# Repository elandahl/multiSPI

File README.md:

# multiSPI
Multiple SPI Devices on a Raspberry Pi

## Description:

Circuit diagram and software to use multiple (> 2) SPI devices on a Raspberry Pi.  This approach uses a shift register to address a demultiplexer which in turn routes up to eight chip selects.  All devices share the same MISO, MOSI, and SCLK.  The Raspberry Pi chip select CE0 is used for SPI communication to the selected device, whereas chip select CE1 is used for latching the shift register.  The particular SPI devices used in this design for demonstration purposes are four 10 bit, 4 differential channel MCP3008 Analog-to-Digital Converters.  Differential voltage measurement is implemented, although the 4 differential measurements could be replaced with eight single inputs.  Another four SPI devices could be added, and this could be further extended with a second demultiplexer to 16 devices.  An additional shft register could be added after the first for essentially unlimited extension to arbitrary numbers of SPI devices.  This same approach could be extended to other platforms such as a microcontroller.

## Author:

Eric Landahl, elandahl@gmail.com

## Acknowledgements:

Motivation from C.D. Landahl

Concept from Ellie Martin-Eberhardt

Requires use of the [C library for Broadcom BCM 2835 as used in Raspberry Pi](http://www.airspayce.com/mikem/bcm2835/index.html) by Mike McCauley.  The code here is based closely on the bcm2835 example file `spin.c`.

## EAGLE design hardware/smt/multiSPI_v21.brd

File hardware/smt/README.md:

Surface Mount design for multiSPI

multiple SPI (> 2) SPI devices on Raspberry Pi. In this case, 4x MCP3008 ADCs. 

OSH Park fabrication in process:  https://oshpark.com/shared_projects/mubjyDKl

This version uses surface mount components and has extra outputs (shift register, CEs, and SPI).s

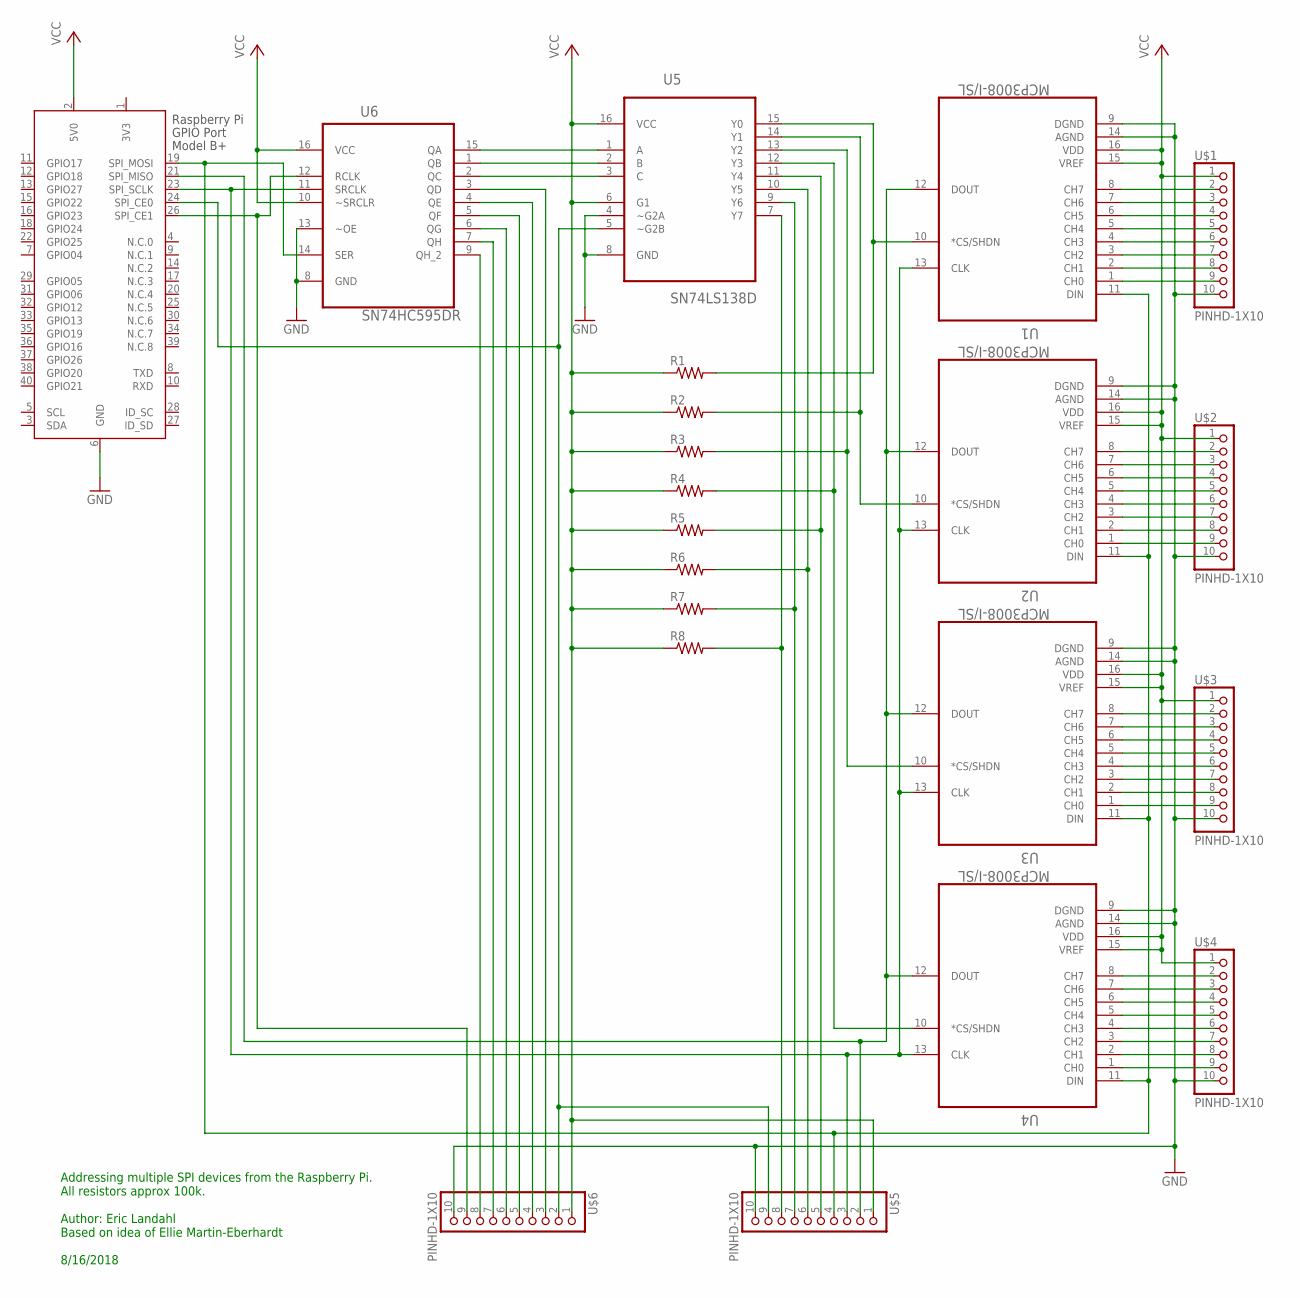
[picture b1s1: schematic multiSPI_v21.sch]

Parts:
R1, R2, R3, R4, R5, R6, R7, R8: R-US_R1210; R1210
U1, U2, U3, U4: MCP3008-I/SL; SOIC127P600X175-16N
U5: SN74LS138D; SOIC127P600X175-16N
U6: SN74HC595DR; SOIC127P600X175-16N
U$1, U$2, U$3, U$4, U$5, U$6: PINHD-1X10; 1X10-BIG
X1: RASPI_GPIO_B+_BOX

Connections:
3V3: X1.1 (3V3)
GND: U1.9 (DGND), U1.14 (AGND), U2.9 (DGND), U2.14 (AGND), U3.9 (DGND), U3.14 (AGND), U4.9 (DGND), U4.14 (AGND), U5.4 (~G2A), U5.8 (GND), U6.8 (GND), U6.13 (~OE), U$1.10, U$2.10, U$3.10, U$4.10, U$5.10, U$6.10, X1.6 (GND)
unnamed: R8.2, U5.7 (Y7), U$5.8
unnamed: R7.2, U5.9 (Y6), U$5.7
unnamed: R6.2, U5.10 (Y5), U$5.6
unnamed: R4.2, U4.10 (*CS/SHDN), U5.12 (Y3)
unnamed: U1.12 (DOUT), U2.12 (DOUT), U3.12 (DOUT), U4.12 (DOUT), U$5.2, X1.21 (SPI_MISO)
unnamed: R3.2, U3.10 (*CS/SHDN), U5.13 (Y2)
unnamed: R5.2, U5.11 (Y4), U$5.5
unnamed: R2.2, U2.10 (*CS/SHDN), U5.14 (Y1)
unnamed: R1.2, U1.10 (*CS/SHDN), U5.15 (Y0)
unnamed: U1.11 (DIN), U2.11 (DIN), U3.11 (DIN), U4.11 (DIN), U6.14 (SER), U$5.4, X1.19 (SPI_MOSI)
unnamed: U6.12 (RCLK), U$6.9, X1.26 (SPI_CE1)
unnamed: U1.8 (CH7), U$1.2
unnamed: U1.7 (CH6), U$1.3
unnamed: U1.6 (CH5), U$1.4
unnamed: U6.9 (QH_2), U$6.8
unnamed: U1.5 (CH4), U$1.5
unnamed: U1.4 (CH3), U$1.6
unnamed: U1.3 (CH2), U$1.7
unnamed: U1.2 (CH1), U$1.8
unnamed: U1.1 (CH0), U$1.9
unnamed: U2.8 (CH7), U$2.2
unnamed: U2.7 (CH6), U$2.3
unnamed: U2.6 (CH5), U$2.4
unnamed: U2.5 (CH4), U$2.5
unnamed: U2.4 (CH3), U$2.6
unnamed: U2.3 (CH2), U$2.7
unnamed: U2.2 (CH1), U$2.8
unnamed: U2.1 (CH0), U$2.9
unnamed: U3.1 (CH0), U$3.9
unnamed: U3.2 (CH1), U$3.8
unnamed: U3.3 (CH2), U$3.7
unnamed: U3.4 (CH3), U$3.6
unnamed: U3.5 (CH4), U$3.5
unnamed: U3.6 (CH5), U$3.4
unnamed: U3.7 (CH6), U$3.3
unnamed: U3.8 (CH7), U$3.2
unnamed: U4.1 (CH0), U$4.9
unnamed: U4.2 (CH1), U$4.8
unnamed: U4.3 (CH2), U$4.7
unnamed: U4.4 (CH3), U$4.6
unnamed: U4.5 (CH4), U$4.5
unnamed: U4.6 (CH5), U$4.4
unnamed: U4.7 (CH6), U$4.3
unnamed: U4.8 (CH7), U$4.2
unnamed: U1.13 (CLK), U2.13 (CLK), U3.13 (CLK), U4.13 (CLK), U6.11 (SRCLK), U$5.3, X1.23 (SPI_SCLK)
unnamed: U5.5 (~G2B), U$5.9, U$6.2, X1.24 (SPI_CE0)
unnamed: U6.7 (QH), U$6.7
unnamed: U6.6 (QG), U$6.6
unnamed: U6.5 (QF), U$6.5
unnamed: U6.4 (QE), U$6.4
unnamed: U6.3 (QD), U$6.3
unnamed: U5.3 (C), U6.2 (QC)
unnamed: U5.2 (B), U6.1 (QB)
unnamed: U5.1 (A), U6.15 (QA)
VCC: R1.1, R2.1, R3.1, R4.1, R5.1, R6.1, R7.1, R8.1, U1.15 (VREF), U1.16 (VDD), U2.15 (VREF), U2.16 (VDD), U3.15 (VREF), U3.16 (VDD), U4.15 (VREF), U4.16 (VDD), U5.6 (G1), U5.16 (VCC), U6.10 (~SRCLR), U6.16 (VCC), U$1.1, U$2.1, U$3.1, U$4.1, U$5.1, U$6.1, X1.2 (5V0)

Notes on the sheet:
Addressing multiple SPI devices from the Raspberry Pi. All resistors approx 100k. Author: Eric Landahl Based on idea of Ellie Martin-Eberhardt 8/16/2018

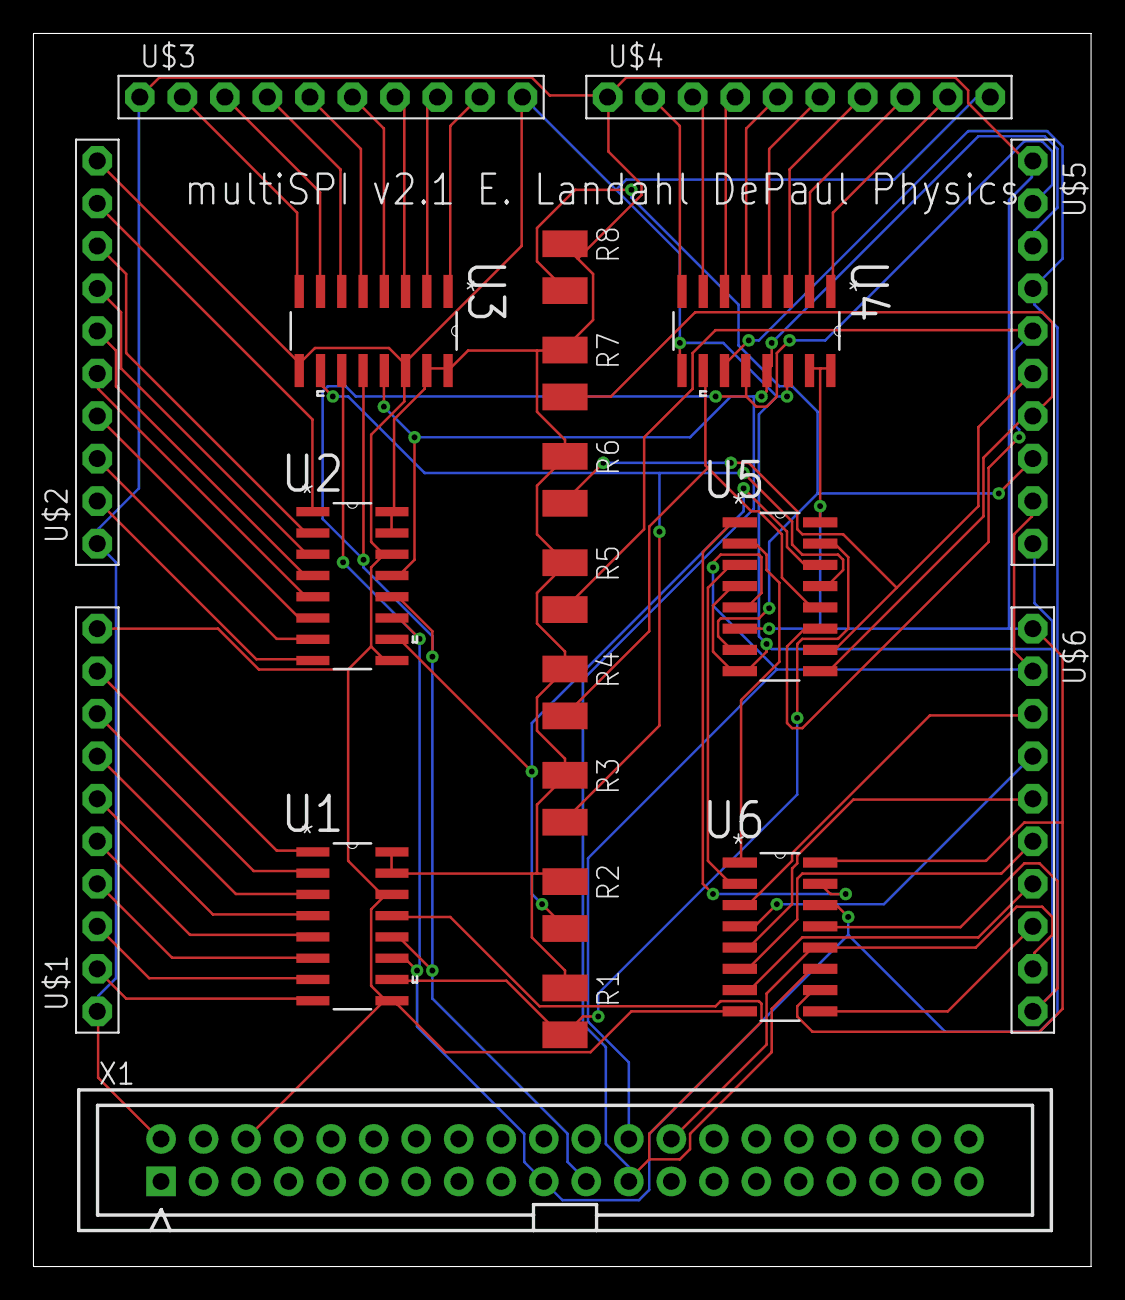
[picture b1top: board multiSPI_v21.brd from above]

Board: 2 copper layers, 63.2 x 73.7 mm, 21 parts (0 on the bottom side), 56 nets.

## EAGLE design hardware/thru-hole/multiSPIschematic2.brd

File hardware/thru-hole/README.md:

# Hardware design files for multiSPI test board

## Contents
Schematic prepared in EAGLE 9.1.0, and using DIP format comonents

Available as .png, .pdf, and EAGLE .sch files

PCB files are now also attached as .brd and well as an image as multiSPI2.pdf

First PCB has been ordered from OSH Park!  [https://oshpark.com/shared_projects/Ye1AAnSY](https://oshpark.com/shared_projects/Ye1AAnSY)

## Hardware used for tests

1. Raspberry Pi Model 3B running Raspbian GNU/Linux 8.0 (jessie)
2. Canakit cobbler breakout 
3. Full size solderless breadboard
4. Shift Register: SN74HC595N
5. Demultiplexer: T74LS138B1
6. ADC (QTY = 2 tested, QTY = 4 in circuit diagram): MCP3008
7. Pullup resistors on multi-chip select lines: (QTY = 2 or 4) approximately 100 kOhm

## Notes
Pin 13 on the 74595 is labeled as "G" on the schematic but appears instead as "~OE" on most datasheets, for "complimentary output enable".  It should be connected to GND for this application.

There is a missing GND on one of the terminal headers.

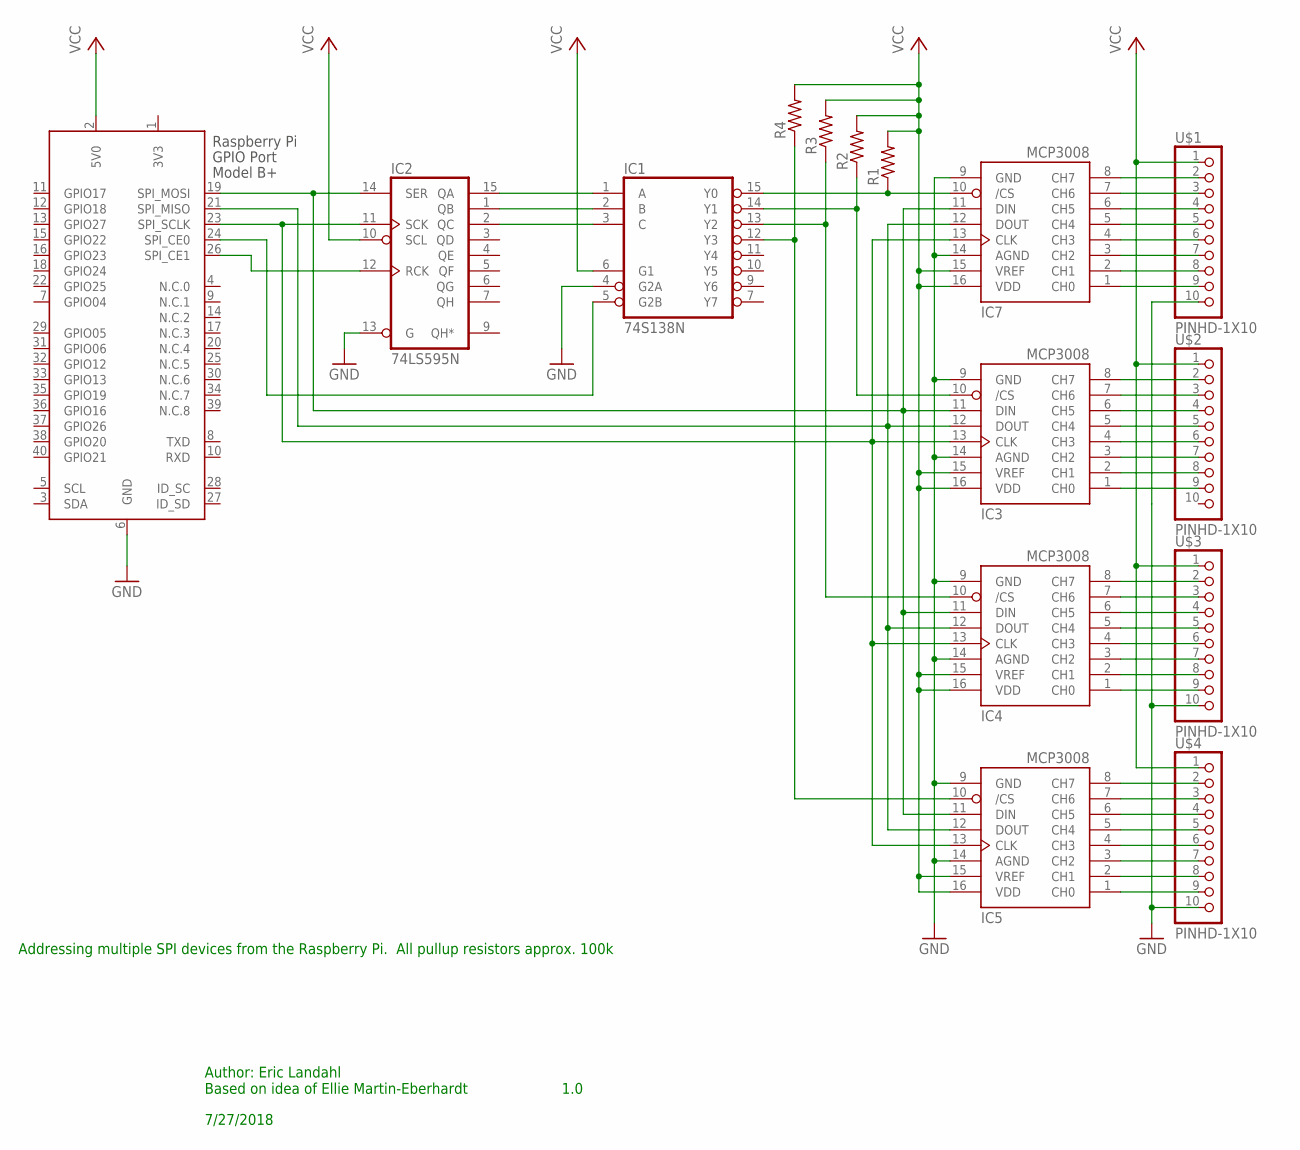
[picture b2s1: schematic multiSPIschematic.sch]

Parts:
IC1: 74S138N; DIL16
IC2: 74LS595N; DIL16
IC3, IC4, IC5, IC7: MCP3008; DIL16
R1, R2, R3, R4: R-US_0207/10; 0207/10
U$1, U$2, U$3, U$4: PINHD-1X10; 1X10-BIG
X1: RASPI_GPIO_B+_BOX

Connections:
3V3: X1.1 (3V3)
GND: IC1.4 (G2A), IC1.8 (GND), IC2.8 (GND), IC2.13 (G), IC3.9 (GND), IC3.14 (AGND), IC4.9 (GND), IC4.14 (AGND), IC5.9 (GND), IC5.14 (AGND), IC7.9 (GND), IC7.14 (AGND), U$1.10, U$3.10, U$4.10, X1.6 (GND)
unnamed: IC1.1 (A), IC2.15 (QA)
unnamed: IC1.2 (B), IC2.1 (QB)
unnamed: IC1.3 (C), IC2.2 (QC)
unnamed: IC2.11 (SCK), IC3.13 (CLK), IC4.13 (CLK), IC5.13 (CLK), IC7.13 (CLK), X1.23 (SPI_SCLK)
unnamed: IC3.12 (DOUT), IC4.12 (DOUT), IC5.12 (DOUT), IC7.12 (DOUT), X1.21 (SPI_MISO)
unnamed: IC1.15 (Y0), IC7.10 (/CS), R1.1
unnamed: IC2.14 (SER), IC3.11 (DIN), IC4.11 (DIN), IC5.11 (DIN), IC7.11 (DIN), X1.19 (SPI_MOSI)
unnamed: IC1.13 (Y2), IC4.10 (/CS), R3.1
unnamed: IC1.14 (Y1), IC3.10 (/CS), R2.1
unnamed: IC1.12 (Y3), IC5.10 (/CS), R4.1
unnamed: IC2.12 (RCK), X1.26 (SPI_CE1)
unnamed: IC7.8 (CH7), U$1.2
unnamed: IC7.7 (CH6), U$1.3
unnamed: IC7.6 (CH5), U$1.4
unnamed: IC1.5 (G2B), X1.24 (SPI_CE0)
unnamed: IC7.5 (CH4), U$1.5
unnamed: IC7.4 (CH3), U$1.6
unnamed: IC7.3 (CH2), U$1.7
unnamed: IC7.2 (CH1), U$1.8
unnamed: IC7.1 (CH0), U$1.9
unnamed: IC3.8 (CH7), U$2.2
unnamed: IC3.7 (CH6), U$2.3
unnamed: IC3.6 (CH5), U$2.4
unnamed: IC3.5 (CH4), U$2.5
unnamed: IC3.4 (CH3), U$2.6
unnamed: IC3.3 (CH2), U$2.7
unnamed: IC3.2 (CH1), U$2.8
unnamed: IC3.1 (CH0), U$2.9
unnamed: IC4.1 (CH0), U$3.9
unnamed: IC4.2 (CH1), U$3.8
unnamed: IC4.3 (CH2), U$3.7
unnamed: IC4.4 (CH3), U$3.6
unnamed: IC4.5 (CH4), U$3.5
unnamed: IC4.6 (CH5), U$3.4
unnamed: IC4.7 (CH6), U$3.3
unnamed: IC4.8 (CH7), U$3.2
unnamed: IC5.1 (CH0), U$4.9
unnamed: IC5.2 (CH1), U$4.8
unnamed: IC5.3 (CH2), U$4.7
unnamed: IC5.4 (CH3), U$4.6
unnamed: IC5.5 (CH4), U$4.5
unnamed: IC5.6 (CH5), U$4.4
unnamed: IC5.7 (CH6), U$4.3
unnamed: IC5.8 (CH7), U$4.2
VCC: IC1.6 (G1), IC1.16 (VCC), IC2.10 (SCL), IC2.16 (VCC), IC3.15 (VREF), IC3.16 (VDD), IC4.15 (VREF), IC4.16 (VDD), IC5.15 (VREF), IC5.16 (VDD), IC7.15 (VREF), IC7.16 (VDD), R1.2, R2.2, R3.2, R4.2, U$1.1, U$2.1, U$3.1, U$4.1, X1.2 (5V0)

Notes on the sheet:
Addressing multiple SPI devices from the Raspberry Pi. All pullup resistors approx. 100k
Author: Eric Landahl Based on idea of Ellie Martin-Eberhardt
1.0
7/27/2018

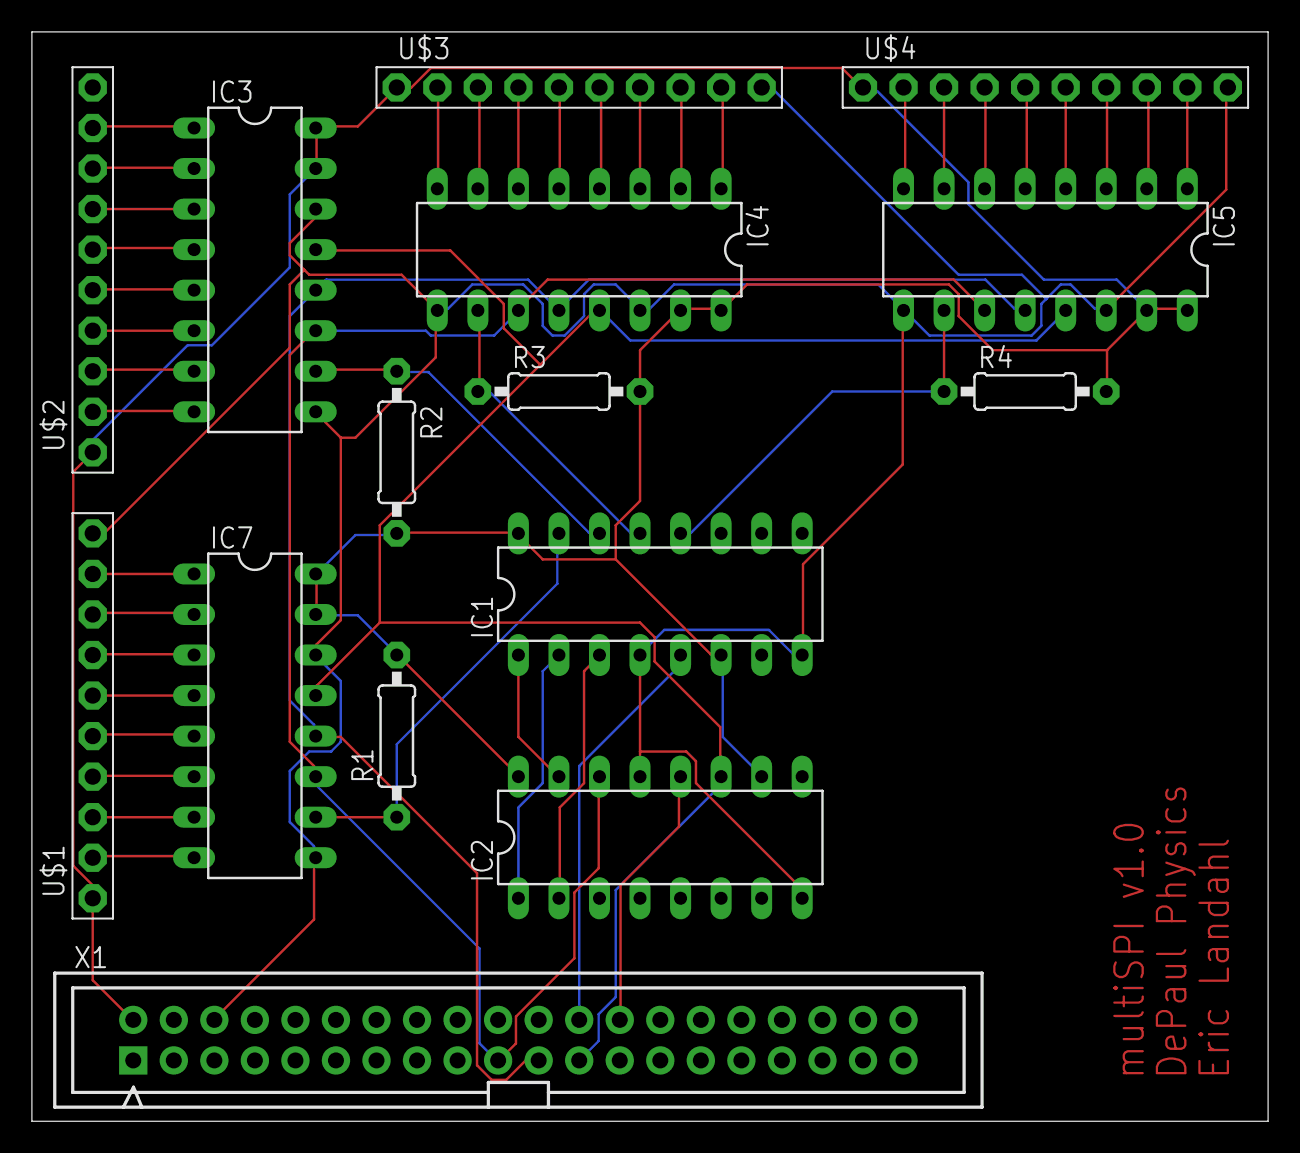
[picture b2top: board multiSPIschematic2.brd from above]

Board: 2 copper layers, 77.5 x 68.2 mm, 15 parts (0 on the bottom side), 46 nets.

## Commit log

2018-07-27 initial README
2018-07-27 first commit of README
2018-07-27 Rename README.md to SRC_README.md
2018-07-27 Rename SRC_README.md to README.md
2018-07-27 include acknowledgements and bcm2835 library link
2018-07-27 added note on 74595 Pin 13
2018-07-27 photo of test board with 2x ADCs
2018-07-30 EAGLE .brd file for making PCB
    submitted to OSH Park July 30, 2018
2018-07-30 routed result for PCB file
2018-07-30 PCB Board files added
2018-08-20 new folder for thru-hole version
2018-08-20 Add files via upload
    thru-hold hardware files
2018-08-20 create folder for surface mount design
2018-08-20 create new folder for surface mount design
